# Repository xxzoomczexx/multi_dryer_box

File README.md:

# 📦 Multi-Box Filament Dryer System

IoT systém pro monitorování a řízení více filamentových sušiček současně. Real-time přehled o stavu materiálu (váha, teplota, vlhkost) v dashboardu s možností přímé integrace do systémů chytré domácnosti a 3D tiskových serverů.

---

## 🌐 Live Demo

**Prohlédněte si běžící webový dashboard zde:**  
👉 **[https://xxzoomczexx.github.io/multi_dryer_box/](https://xxzoomczexx.github.io/multi_dryer_box/)**

*(Dashboard funguje jako statická vizualizace MQTT dat z připojených hardwarových sušiček).*

---

## 🚀 Rychlý návod k sestavení pro Raspberry Pi Pico W / Pico 2 W

Master Node se připojuje přímo přes **Wi-Fi** a **MQTT protocol (lwIP)** na cloudový broker bez nutnosti mít spuštěný jakýkoliv skript na PC.

### 1. Konfigurace Wi-Fi přístupových údajů

Před kompilací zkontrolujte v kořenu projektu soubor `config.h` (můžete zkopírovat ze šablony `config.h.example`):

```bash
cp config.h.example config.h
```

Otevřete `config.h` a zadejte název a heslo k vaší Wi-Fi síti:

```c
#define WIFI_SSID       "NAZEV_VASI_WIFI"
#define WIFI_PASSWORD   "VASE_HESLO"
```

*(Soubor `config.h` je v `.gitignore`, vaše heslo se nedostane do Git repozitáře).*

### 2. Kompilace a nahrání firmwaru

1. Otevřete projekt ve VS Code s nainstalovaným **Raspberry Pi Pico extension** (Pico SDK 2.x).
2. Sestavte projekt pro **Pico W** (nebo `pico2_w` pro Pico 2 W):
   ```bash
   cmake -B build -S . -DPICO_BOARD=pico_w
   cmake --build build
   ```
3. Zapojte **Raspberry Pi Pico W** v BOOTSEL režimu (se stisknutým tlačítkem BOOTSEL) a nahrajte vygenerovaný soubor `build/drybox_firmware.uf2` přetažením na disk `RPI-RP2`.

---

## 🏗️ Architektura Systému (Data Flow)

Systém je navržen pro modularitu a stabilitu komunikace. Skládá se z několika vrstev:

1. **Sensor Nodes (RP2040):** Každý sušicí box obsahuje vlastní mikrokontrolér, který sbírá data z lokálních senzorů a stará se o topná tělesa.
2. **Master Node (Pico W / Pico 2 W):** Centrální mozek systému. Přijímá data přes CAN/I2C od jednotlivých boxů a posílá je přes Wi-Fi.
3. **Direct MQTT / Wi-Fi (lwIP):** Master Node využívá Wi-Fi stack CYW43439 pro bezpečné odeslání agregovaných dat přes internet k MQTT brokeru.
4. **Cloud Broker:** Zprostředkovatel zpráv (`test.mosquitto.org` / `54.36.178.49`).
5. **Frontend (GitHub Pages):** Koncový klient přistupující k datům přes Secure WebSockets (`wss://test.mosquitto.org:8081/mqtt`) a vizualizující je v reálném čase.

---

## ✨ Klíčové Vlastnosti (Key Features)

- 📡 **Přístup odkudkoliv:** Systém využívá MQTT a nevyžaduje žádný složitý port-forwarding na routeru ani pevnou veřejnou IP adresu.
- ⚡ **Plug & Play Multi-Box:** Automatické generování unikátního ID sušičky z HW MAC adresy. Můžete nahrát jeden `.uf2` soubor na libovolný počet Pico desek bez ručních změn kódu.
- 🔒 **Bezpečné uložení údajů:** Wi-Fi credentials uložené v ignorovaném `config.h`.
- 📊 **Integrace a API:** Architektura otevírá cesty pro integrace do systémů **Home Assistant** a API endpointů tiskových platforem, jako je **Prusa Connect**.

---

## 🛠️ Hardware Details

- **Raspberry Pi Pico W (RP2040) / Pico 2 W (RP2350):** Mikrokontrolér s integrovaným Wi-Fi modulem CYW43439 pro Master Node.
- **Raspberry Pi RP2040:** Cenově dostupné a spolehlivé mikrokontroléry pro jednotlivé podřízené uzly (Sensor Nodes).
- **SHT4x:** Digitální senzory pro měření teploty a relativní vlhkosti uvnitř filamentových boxů.
- **HX711:** 24bitový A/D převodník a tenzometry pro přesné měření hmotnosti a úbytku filamentu.

---

## 💻 Software Stack

| Vrstva | Použitá Technologie | Popis |
| :--- | :--- | :--- |
| **Firmware** | C / C++ (Pico SDK 2.3) | Nízkoúrovňový kód pro sběr dat ze senzorů, Wi-Fi a MQTT komunikaci. |
| **Networking** | lwIP / CYW43 Architecture | Integrovaný síťový stack pro Wi-Fi připojení a MQTT klienta. |
| **Frontend** | HTML5, Vanilla JavaScript | Plně statická single-file aplikace (SPA) hostovaná na GitHub Pages. |
| **Styling & UI** | Tailwind CSS (CDN) | Dark Mode designový systém pro esteticky čisté a responzivní UI prvky. |
| **Vizualizace** | Chart.js | Real-time grafy uchovávající a vykreslující historii úbytku hmotnosti v čase. |
| **Cloud Bridge** | MQTT.js | WebSockets klient pro čtení telemetrie v prohlížeči a odesílání kontrolních příkazů. |

---

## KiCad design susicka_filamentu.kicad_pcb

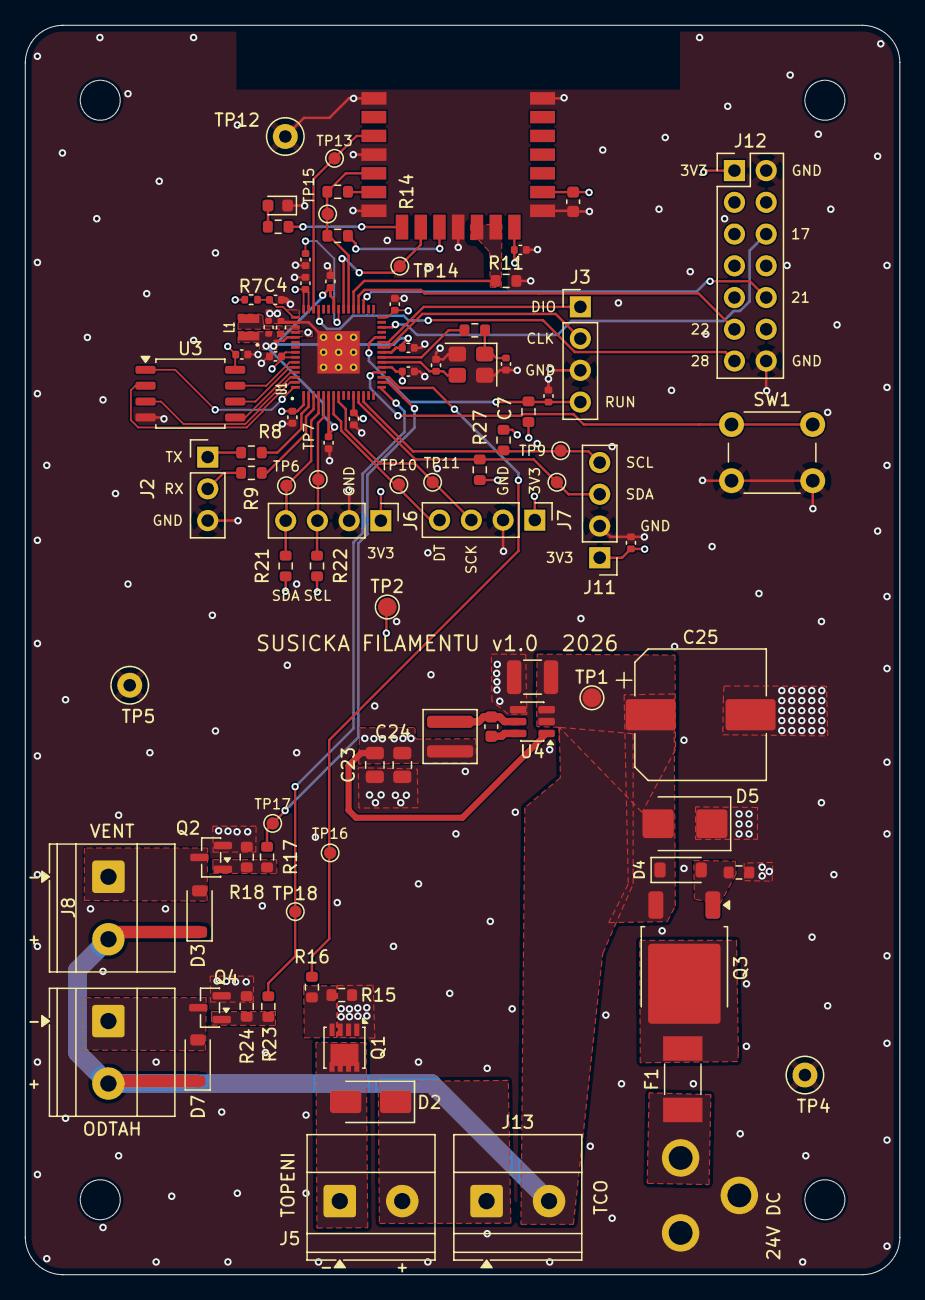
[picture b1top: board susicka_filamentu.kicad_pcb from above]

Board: 4 copper layers, 70.0 x 100.0 mm, 96 parts (0 on the bottom side), 63 nets.

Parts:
C1, C2: 15p; C_0402_1005Metric
C4: 4,7uF; C_0402_1005Metric
C5, C6: 4,7 uF; C_0402_1005Metric_RPi
C7, C8, C9, C10, C11, C12, C13, C14, C15, C16, C17, C18, C20: 100 nF; C_0402_1005Metric
C19: 10 uF; C_0603_1608Metric
C21: 10 uF; C_1210_3225Metric
C22: 100 nF; C_0603_1608Metric
C23, C24: 22 uF; C_0805_2012Metric
C25: 100uF 50V; CP_Elec_10x10
C27: 100nF; C_0402_1005Metric
D2: SS14; D_SMA
D3, D7: B5819W; D_SOD-123
D4: BZT52C15; D_SOD-123
D5: SMBJ24CA; D_SMB
D6: LED zelená; LED_0603_1608Metric
F1: 4A T; Fuse_Littelfuse-NANO2-451_453
H1, H2, H3, H4: M3; MountingHole_3.2mm_M3
J2: Conn_01x03; PinHeader_1x03_P2.54mm_Vertical
J3: Conn_01x04; PinHeader_1x04_P2.54mm_Vertical
J4: PJ-102AH
J5: Topeni 24V; TerminalBlock_Phoenix_MKDS-1,5-2_1x02_P5.00mm_Horizontal
J6: SHT4x; PinHeader_1x04_P2.54mm_Vertical
J7: HX711; PinHeader_1x04_P2.54mm_Vertical
J8: Ventilator 24V; TerminalBlock_Phoenix_MKDS-1,5-2_1x02_P5.00mm_Horizontal
J9: Odtah 24V; TerminalBlock_Phoenix_MKDS-1,5-2_1x02_P5.00mm_Horizontal
J11: SHT40 #2; PinHeader_1x04_P2.54mm_Vertical
J12: GPIO rezerva; PinHeader_2x07_P2.54mm_Vertical
J13: Tepelna pojistka; TerminalBlock_Phoenix_MKDS-1,5-2_1x02_P5.00mm_Horizontal
L1: AOTA-B201610S3R3-101-T; L_Abracon_AOTA-B201610
L2: 4,7uH; L_Wuerth_MAPI-4020
Q1: SiS434DN; Vishay_PowerPAK_1212-8_Single_GSD
Q2, Q4: AO3422; SOT-23
Q3: AOD4185; TO-252-2
R1: 1k; R_0603_1608Metric
R7: 33; R_0402_1005Metric
R8, R9, R20: 220; R_0603_1608Metric
R10, R11, R13, R19: 10k; R_0603_1608Metric
R14: 470; R_0603_1608Metric
R15, R18, R24: 100k; R_0603_1608Metric
R16, R17, R23: 100; R_0603_1608Metric
R21, R22, R26, R27: 4k7; R_0603_1608Metric
SW1: Tlacitko; SW_PUSH_6mm
TP1: 24V; TestPoint_Pad_D1.5mm
TP2: +3V3; TestPoint_Pad_D1.5mm
TP4, TP5, TP12: GND; TestPoint_Loop_D2.50mm_Drill1.0mm
TP6: SDA; TestPoint_Pad_D1.0mm
TP7: SCL; TestPoint_Pad_D1.0mm
TP8: SDA0; TestPoint_Pad_D1.0mm
TP9: SCL0; TestPoint_Pad_D1.0mm
TP10: HX711_DT; TestPoint_Pad_D1.0mm
TP11: HX711_SCK; TestPoint_Pad_D1.0mm
TP13: WL_CLK; TestPoint_Pad_D1.0mm
TP14: WL_CS; TestPoint_Pad_D1.0mm
TP15: WL_DATA; TestPoint_Pad_D1.0mm
TP16: HEAT_PWM; TestPoint_Pad_D1.0mm
TP17: FAN_PWM; TestPoint_Pad_D1.0mm
TP18: EXH_PWM; TestPoint_Pad_D1.0mm
U1: RP2350A-QFN60; RP2350A_QFN-60_RPi_Minimal
U2: RM2; rpi_rmc20452t
U3: W25Q128JVS; SOIC-8_5.3x5.3mm_P1.27mm
U4: AP63203WU; TSOT-23-6
Y1: ABM8-272-T3 12MHz; Crystal_SMD_3225-4Pin_3.2x2.5mm

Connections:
24V: C21.1, C25.1, D3.1 (K), D4.1 (K), D5.2 (A2), D7.1 (K), J8.2, J9.2, J13.2, Q3.3 (S), TP1.1, U4.2 (EN), U4.3 (IN)
24V_IN: F1.1, J4.1
+1V1: C5.1, C15.1, C16.1, C17.1, L1.1, U1.6 (DVDD), U1.23 (DVDD), U1.39 (DVDD), U1.50 (VREG_FB)
+3V3: C6.1, C8.1, C9.1, C10.1, C11.1, C12.1, C13.1, C14.1, C18.1, C19.1, C20.1, C23.1, C24.1, C27.1, J6.1, J7.1, J11.1, J12.1, L2.2, R7.1, R10.2, R21.1, R22.1, R26.1, R27.1, TP2.1, U1.1 (IOVDD), U1.11 (IOVDD), U1.20 (IOVDD), U1.30 (IOVDD), U1.38 (IOVDD), U1.44 (ADC_AVDD), U1.45 (IOVDD), U1.49 (VREG_VIN), U1.53 (USB_OTP_VDD), U1.54 (QSPI_IOVDD), U2.14 (VDDIO), U2.16 (VIN), U3.8 (VCC), U4.1 (FB)
/RM2/RM2_BT_ON: R11.1, U1.35 (GPIO23), U2.12 (WL_ON), U2.13 (BT_ON)
/flash/QSPI_SCLK: U1.56 (QSPI_SCLK), U3.6 (CLK)
/flash/QSPI_SD0: U1.57 (QSPI_SD0), U3.5 (DI/IO_{0})
/flash/QSPI_SD1: U1.59 (QSPI_SD1), U3.2 (DO/IO_{1})
/flash/QSPI_SD2: U1.58 (QSPI_SD2), U3.3 (~WP/IO_{2})
/flash/QSPI_SD3: U1.55 (QSPI_SD3), U3.7 (~HOLD/~RESET/IO_{3})
/flash/QSPI_SS: U1.60 (QSPI_SS), U3.1 (~CS)
/oscillator/XIN: C1.2, U1.21 (XIN), Y1.3
/oscillator/XOUT: R1.2, U1.22 (XOUT)
/vystupy/HEAT_V: D2.1 (K), J5.2, J13.1
BTN: SW1.1, U1.19 (GPIO15)
EXH_PWM: R23.1, TP18.1, U1.16 (GPIO12)
FAN_PWM: R17.1, TP17.1, U1.17 (GPIO13)
GND: C1.1, C2.1, C4.2, C5.2, C6.2, C7.1, C8.2, C9.2, C10.2, C11.2, C12.2, C13.2, C14.2, C15.2, C16.2, C17.2, C18.2, C19.2, C20.2, C21.2, C23.2, C24.2, C25.2, C27.2, D5.1 (A1), D6.1 (K), J2.3, J3.3, J4.2, J4.3, J6.2, J7.2, J11.2, J12.2, J12.14, Q1.2 (S), Q2.2 (S), Q4.2 (S), R11.2, R15.2, R18.2, R19.2, R24.2, SW1.2, TP4.1, TP5.1, TP12.1, U1.47 (VREG_PGND), U1.61 (GND), U2.1 (GND), U2.4 (GND), U2.7 (GND), U2.11 (GND), U2.15 (GND), U2.21 (GND), U3.4 (GND), U4.4 (GND), Y1.2, Y1.4
GP10: J12.3, U1.14 (GPIO10)
GP11: J12.4, U1.15 (GPIO11)
GP16: J12.5, U1.27 (GPIO16)
GP17: J12.6, U1.28 (GPIO17)
GP18: J12.7, U1.29 (GPIO18)
GP19: J12.8, U1.31 (GPIO19)
GP20: J12.9, U1.32 (GPIO20)
GP21: J12.10, U1.33 (GPIO21)
GP22: J12.11, U1.34 (GPIO22)
GP27: J12.12, U1.41 (GPIO27_ADC1)
GP28: J12.13, U1.42 (GPIO28_ADC2)
HEAT_PWM: R16.1, TP16.1, U1.18 (GPIO14)
HX711_DT: J7.4, TP10.1, U1.7 (GPIO4)
HX711_SCK: J7.3, TP11.1, U1.8 (GPIO5)
unnamed: C2.2, R1.1, Y1.1
unnamed: D2.2 (A), J5.1, Q1.3 (D)
unnamed: D3.2 (A), J8.1, Q2.3 (D)
unnamed: D4.2 (A), Q3.1 (G), R19.1
unnamed: D6.2 (A), R20.2
unnamed: D7.2 (A), J9.1, Q4.3 (D)
unnamed: J2.1, R8.2
unnamed: J2.2, R9.2
unnamed: C7.2, J3.4, R10.1, U1.26 (RUN)
unnamed: Q1.1 (G), R15.1, R16.2
unnamed: Q2.1 (G), R17.2, R18.1
unnamed: F1.2, Q3.2 (D)
unnamed: Q4.1 (G), R23.2, R24.1
unnamed: R8.1, U1.2 (GPIO0)
unnamed: R9.1, U1.3 (GPIO1)
unnamed: C4.1, R7.2, U1.46 (VREG_AVDD)
unnamed: L1.2, U1.48 (VREG_LX)
unnamed: R14.2, U2.6 (DO)
unnamed: R13.2, U2.10 (nIRQ)
unnamed: C22.2, U4.6 (BST)
unnamed: C22.1, L2.1, U4.5 (SW)
SCL: J6.3, R22.2, TP7.1, U1.5 (GPIO3)
SCL0: J11.4, R27.2, TP9.1, U1.13 (GPIO9)
SDA: J6.4, R21.2, TP6.1, U1.4 (GPIO2)
SDA0: J11.3, R26.2, TP8.1, U1.12 (GPIO8)
SWCLK: J3.2, U1.24 (SWCLK)
SWDIO: J3.1, U1.25 (SWDIO)
WL_CLK: TP13.1, U1.43 (GPIO29_ADC3), U2.3 (SCLK)
WL_CS: TP14.1, U1.37 (GPIO25), U2.9 (CS)
WL_DATA: R13.1, R14.1, TP15.1, U1.36 (GPIO24), U2.5 (DI)
WL_GPIO0: R20.1, U2.8 (GPIO0)

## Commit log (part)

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2026-05-07 Add real-time MQTT Drybox Dashboard
2026-05-07 Docs: Přidání kompletní dokumentace projektu
2026-05-07 Refine README content and formatting
    Updated the README to improve clarity and formatting.
2026-05-07 Refine language in README for better clarity
    Updated the README to improve clarity and readability.
2026-05-07 Update README for clarity and remove unnecessary text
2026-05-12 Prvni upload projektu
